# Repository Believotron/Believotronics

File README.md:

# Believotronics
[website](http://believotron.com/believotronics) | [donate](https://www.patreon.com/Believotron) | [community](http://community.believotron.com/c/believotronics)

Believotronics is a low-cost DIY open source robotics platform you can print and build at work or from home. Our first projects are a MicroscopeBot and a ThroughholeSolderBot.

We also develop mechatronics, jigs, firmware, assemblies, etc. Your basic toolkit for interfacing the physical world with the software world, allowing software to exist in physical space. Robots building robots. That sort of thing.

----
## Current Status

The current focus of the project is the [Core3D OpenSCAD Refactor](/Core3D/readme.md). We've designed the proof of concept using proprietary CAD tools, and now we'd like to convert them all to OpenSCAD, allowing for a much more flexible, modular, and ultimately scalable solution. Once we have the core system redesiged, we will start refactoring the [MircoscopeBot](/MircoscopeBot/.readme), and then then proceed with the [ThroughholeSolderBot](/ThroughholeSolderBot/readme.md)

Each project is maintained and documented in the project subdirectory.

Unless otherwise noted, this project uses the [MIT License](license).

[website](http://believotron.com/believotronics) | [donate](https://www.patreon.com/Believotron) | [community](http://community.believotron.com/c/believotronics)

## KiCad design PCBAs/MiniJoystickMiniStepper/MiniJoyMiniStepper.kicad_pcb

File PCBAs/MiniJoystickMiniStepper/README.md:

# Believotronics MiniJoystickMiniStepper
[website](http://believotron.com/believotronics) | [donate](https://www.patreon.com/Believotron) | [community](http://community.believotron.com/c/believotronics)

Believotronics is a low-cost DIY open source robotics platform you can print and build at work or from home. The MiniJoystickMiniStepper motor is a proof of concept to allow us to start prototyping controls using joysticks and driving motors with the ULM2803s.

Please [consider helping us with your financial support:](https://www.patreon.com/Believotron)

----
## Current Status

Phase 3 (Current): Pause
This project is on hold until the [Core3D](/Core3D/readme.md) refactoring project is complete.

Phase 4:
- Replace joysticks with gamepad style analog thumbsticks
- Increase channel count
- Insert serial buffer ICs to make code more platform agnostic
- Shrink board for Cortex M0 application
- Prototype LiPo / Lion 18650 (Protected) battery power
- Prototype initial Cortex M0 bootstrap (bypass using external controller

Phase 5:
- Add wireless support

[website](http://believotron.com/believotronics) | [donate](https://www.patreon.com/Believotron) | [community](http://community.believotron.com/c/believotronics)

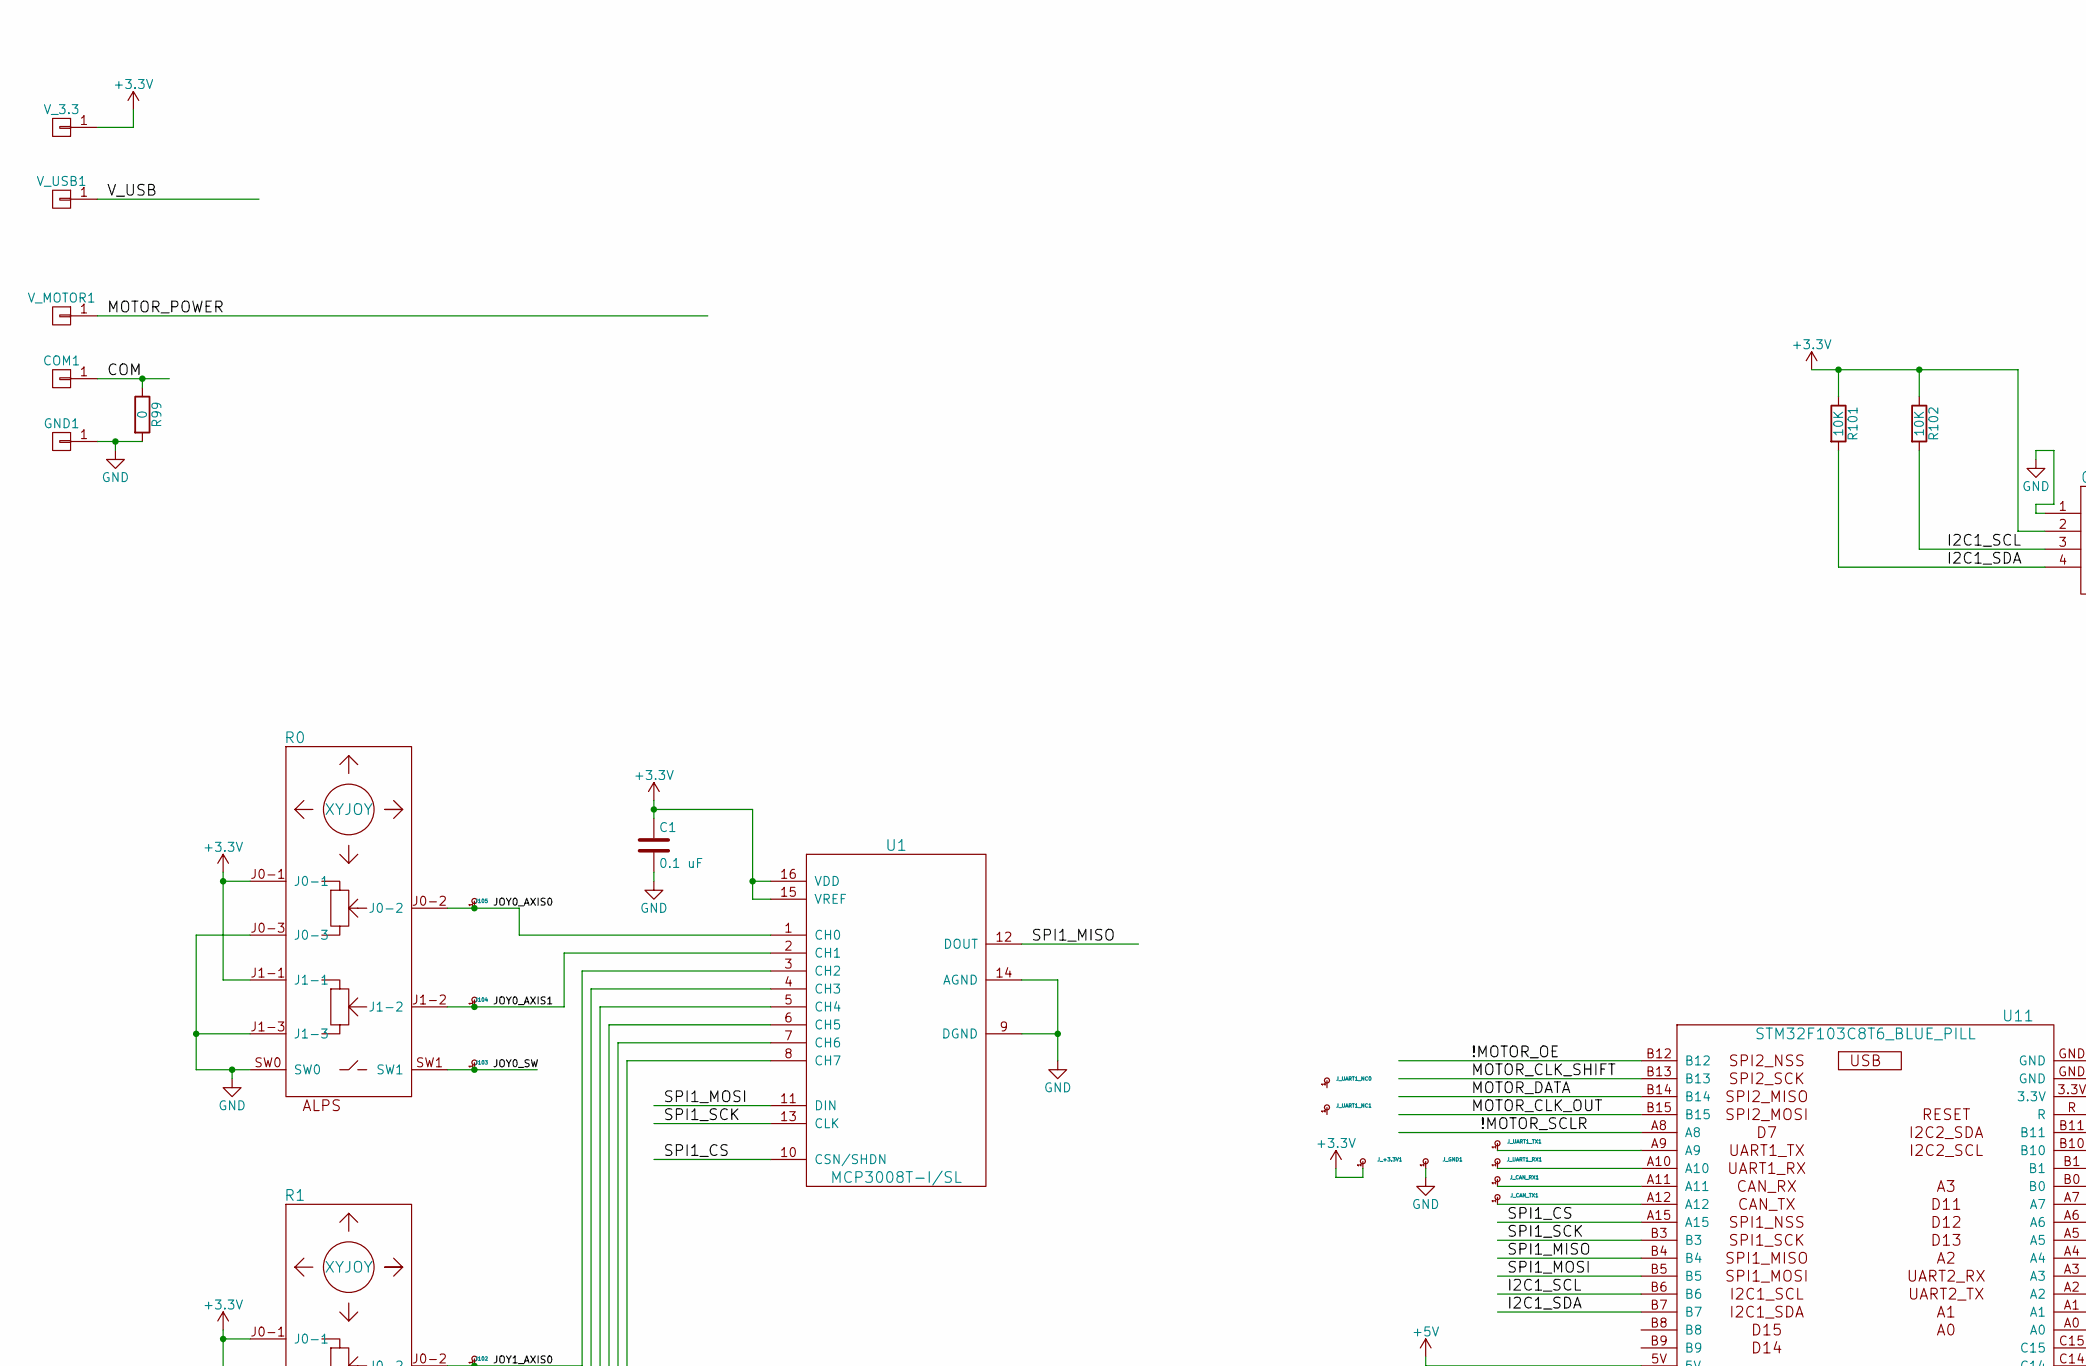
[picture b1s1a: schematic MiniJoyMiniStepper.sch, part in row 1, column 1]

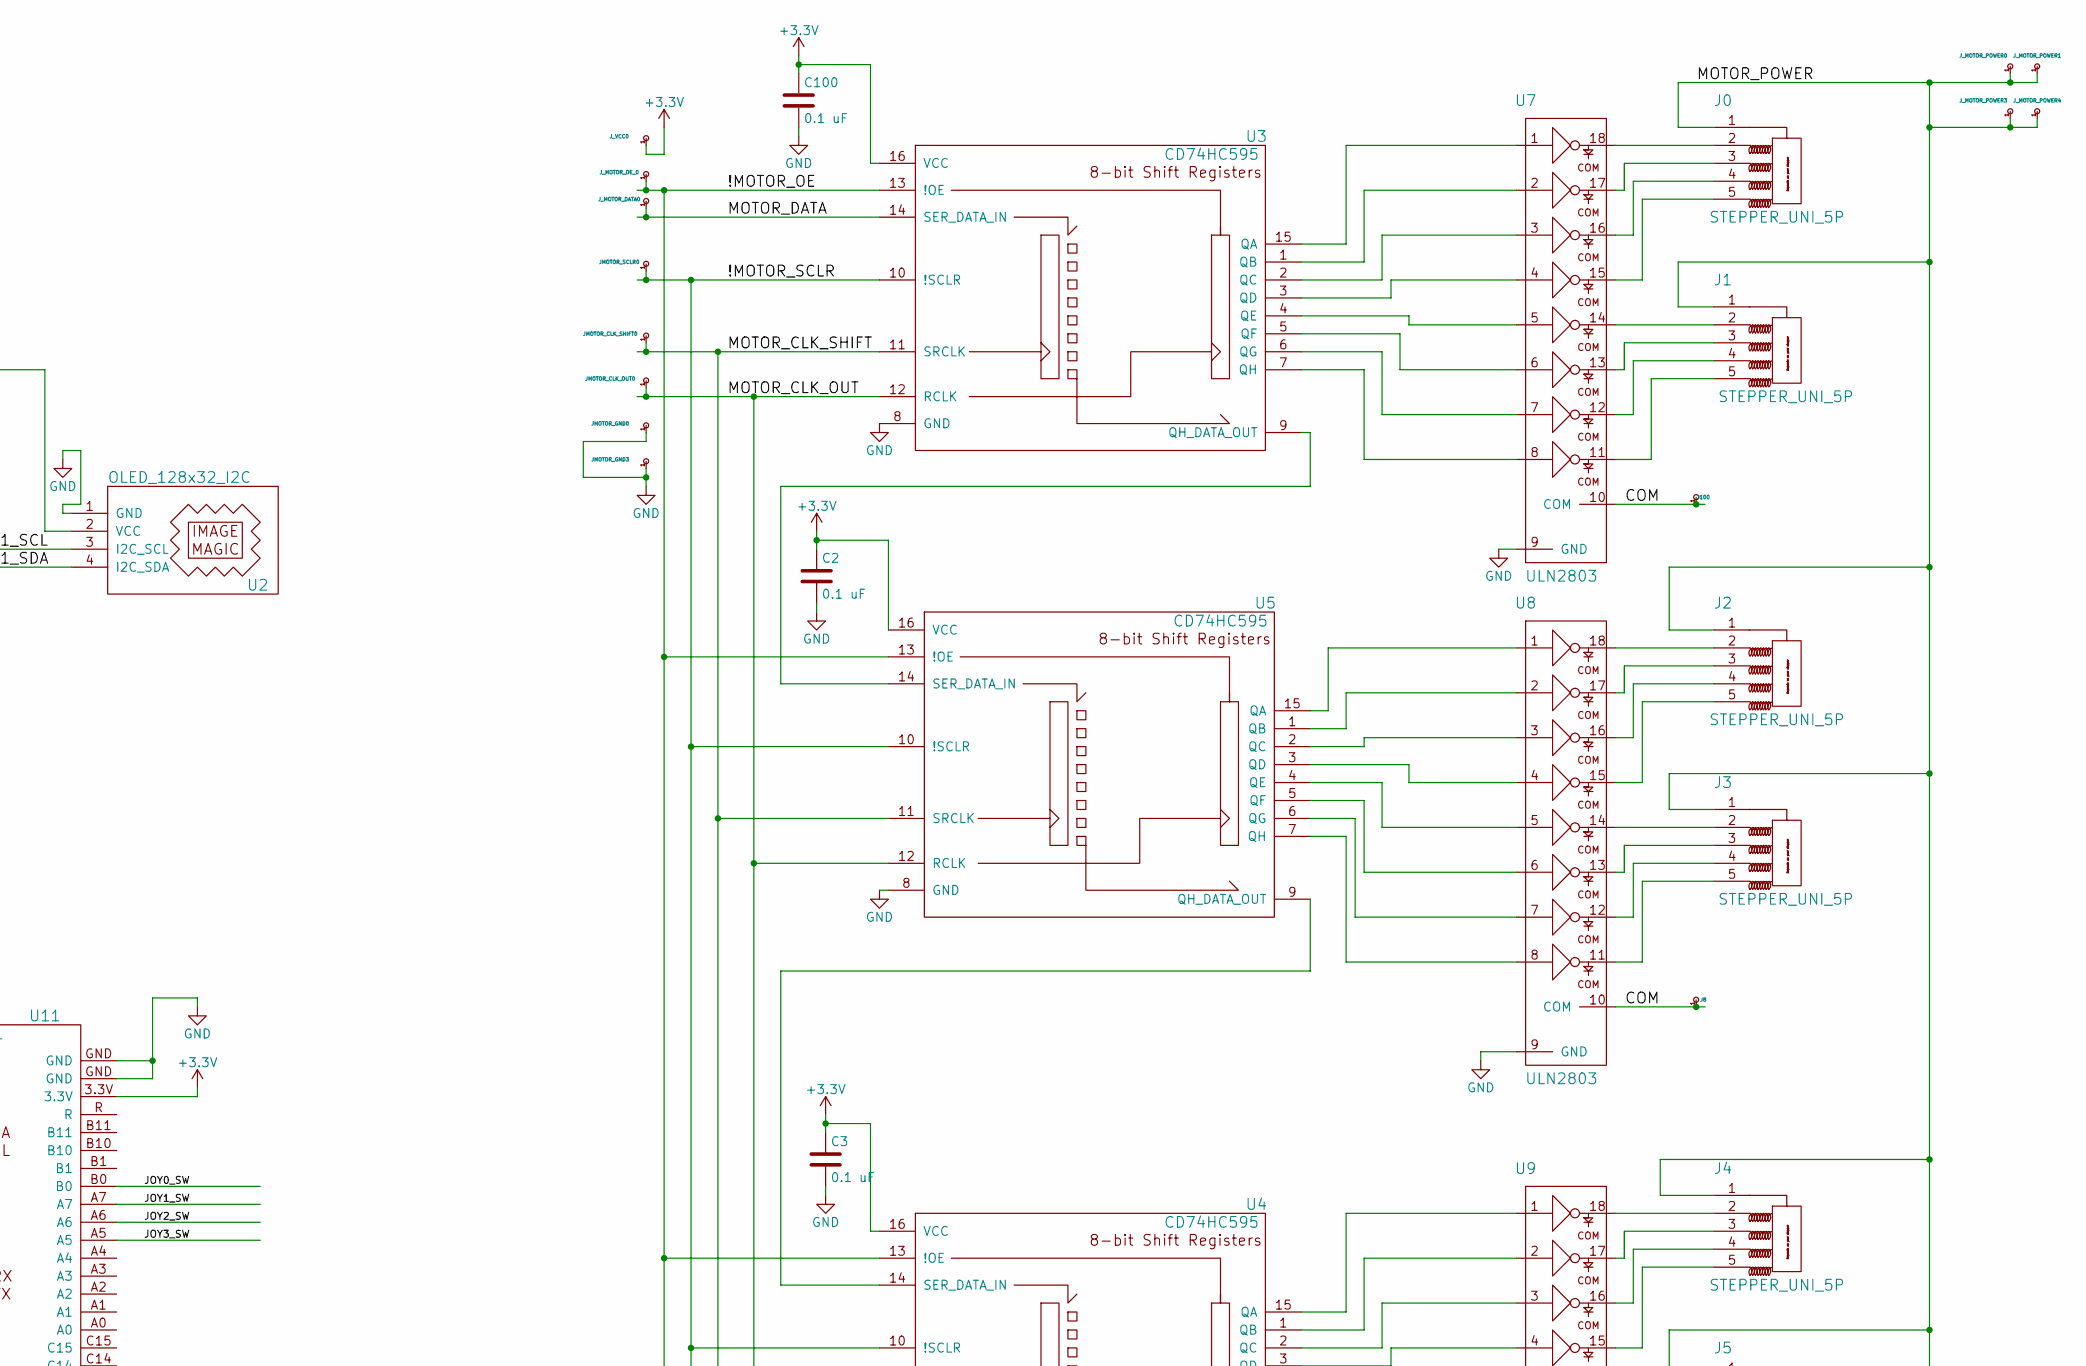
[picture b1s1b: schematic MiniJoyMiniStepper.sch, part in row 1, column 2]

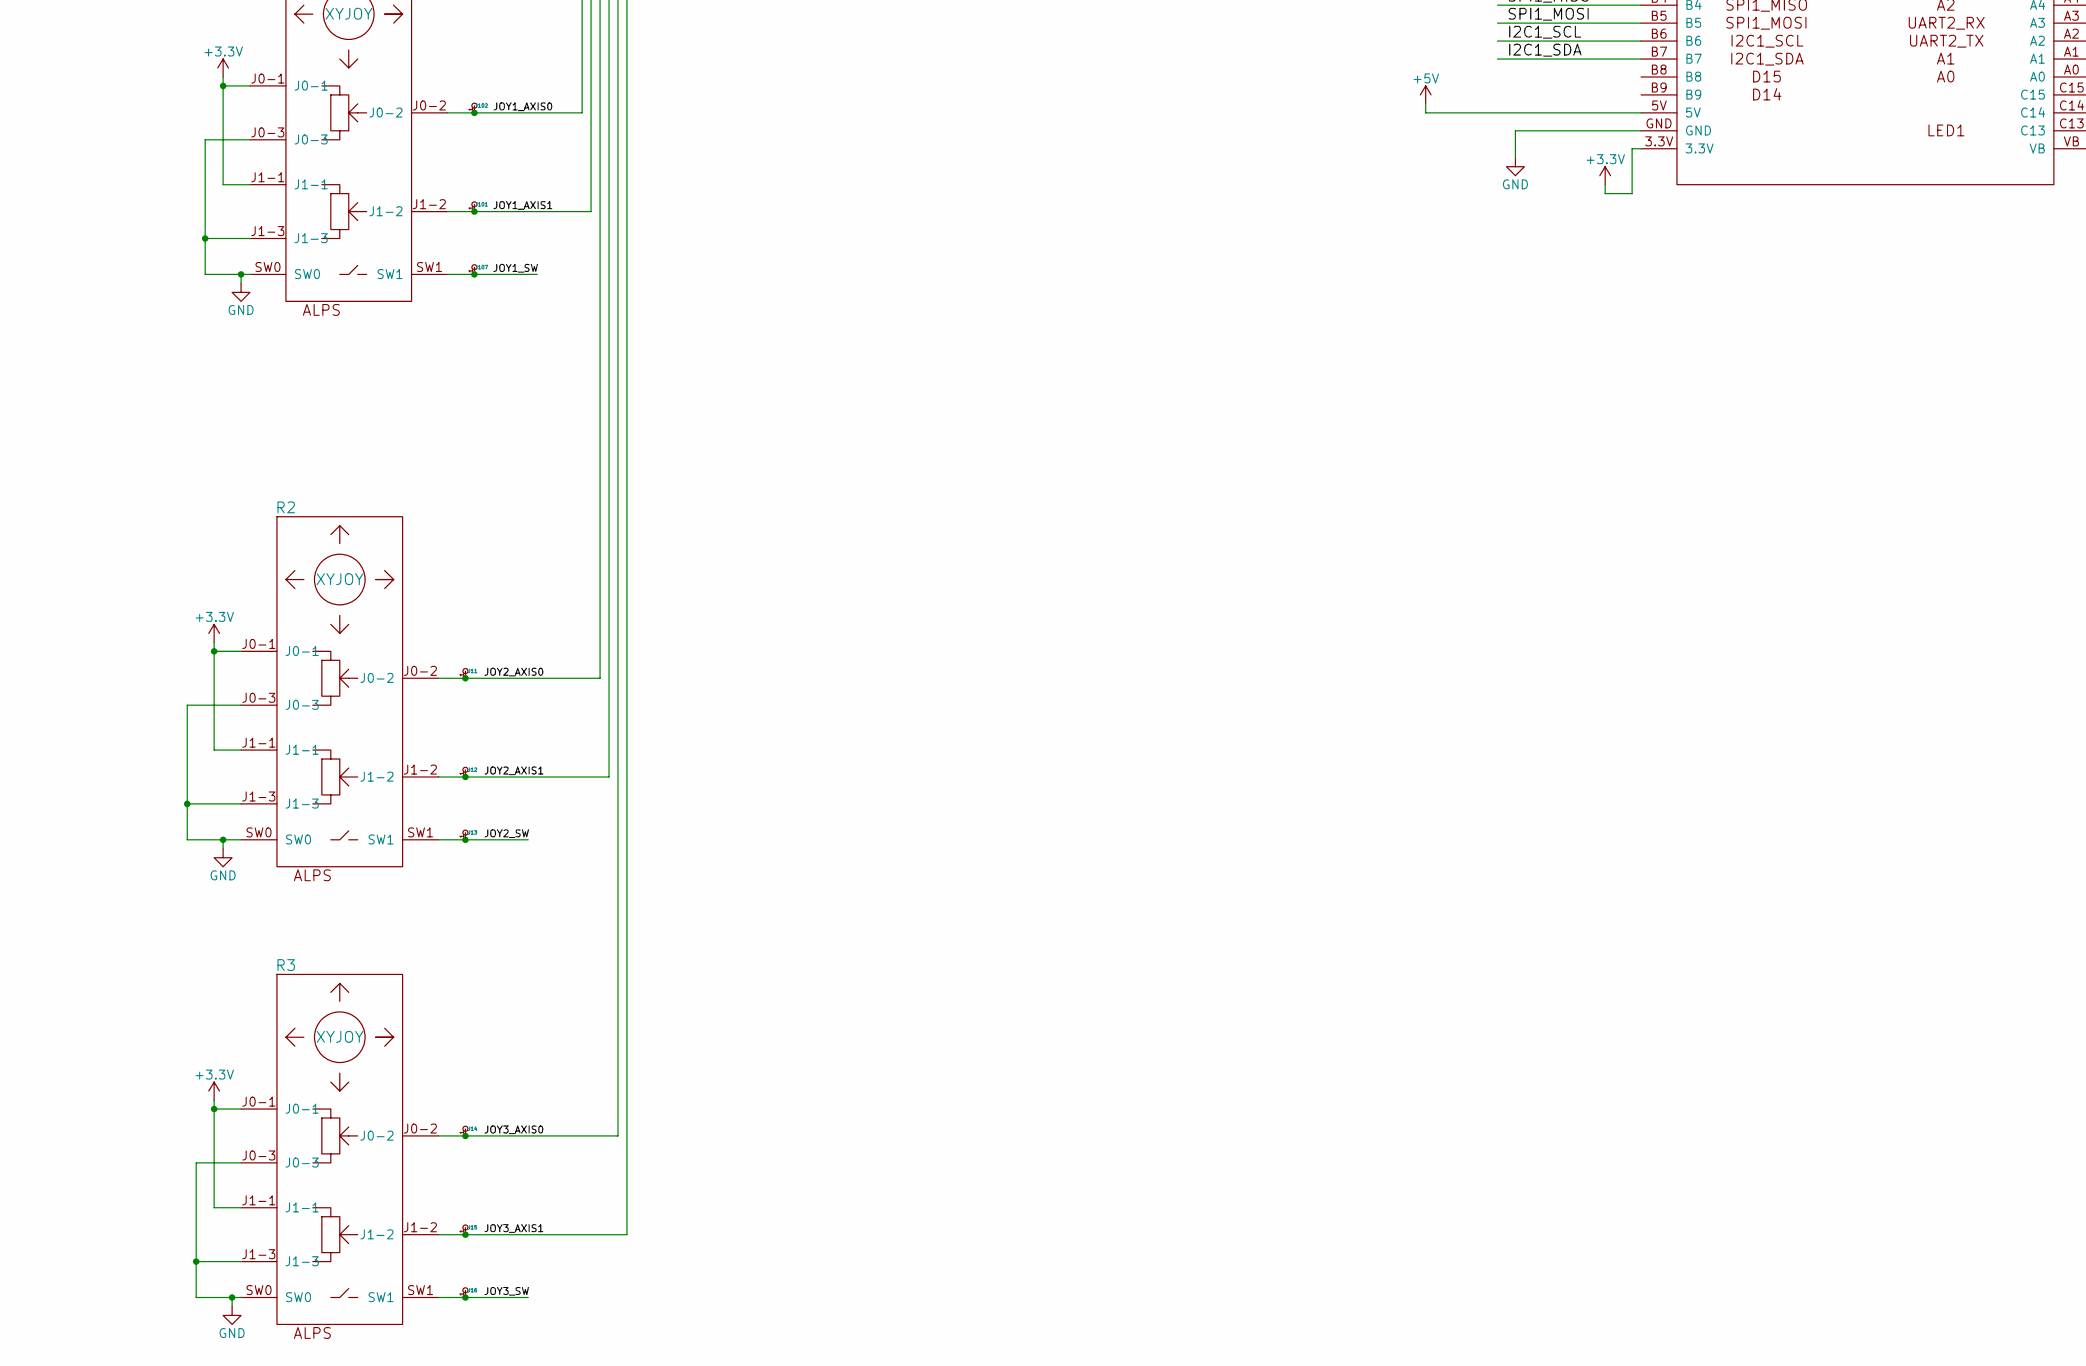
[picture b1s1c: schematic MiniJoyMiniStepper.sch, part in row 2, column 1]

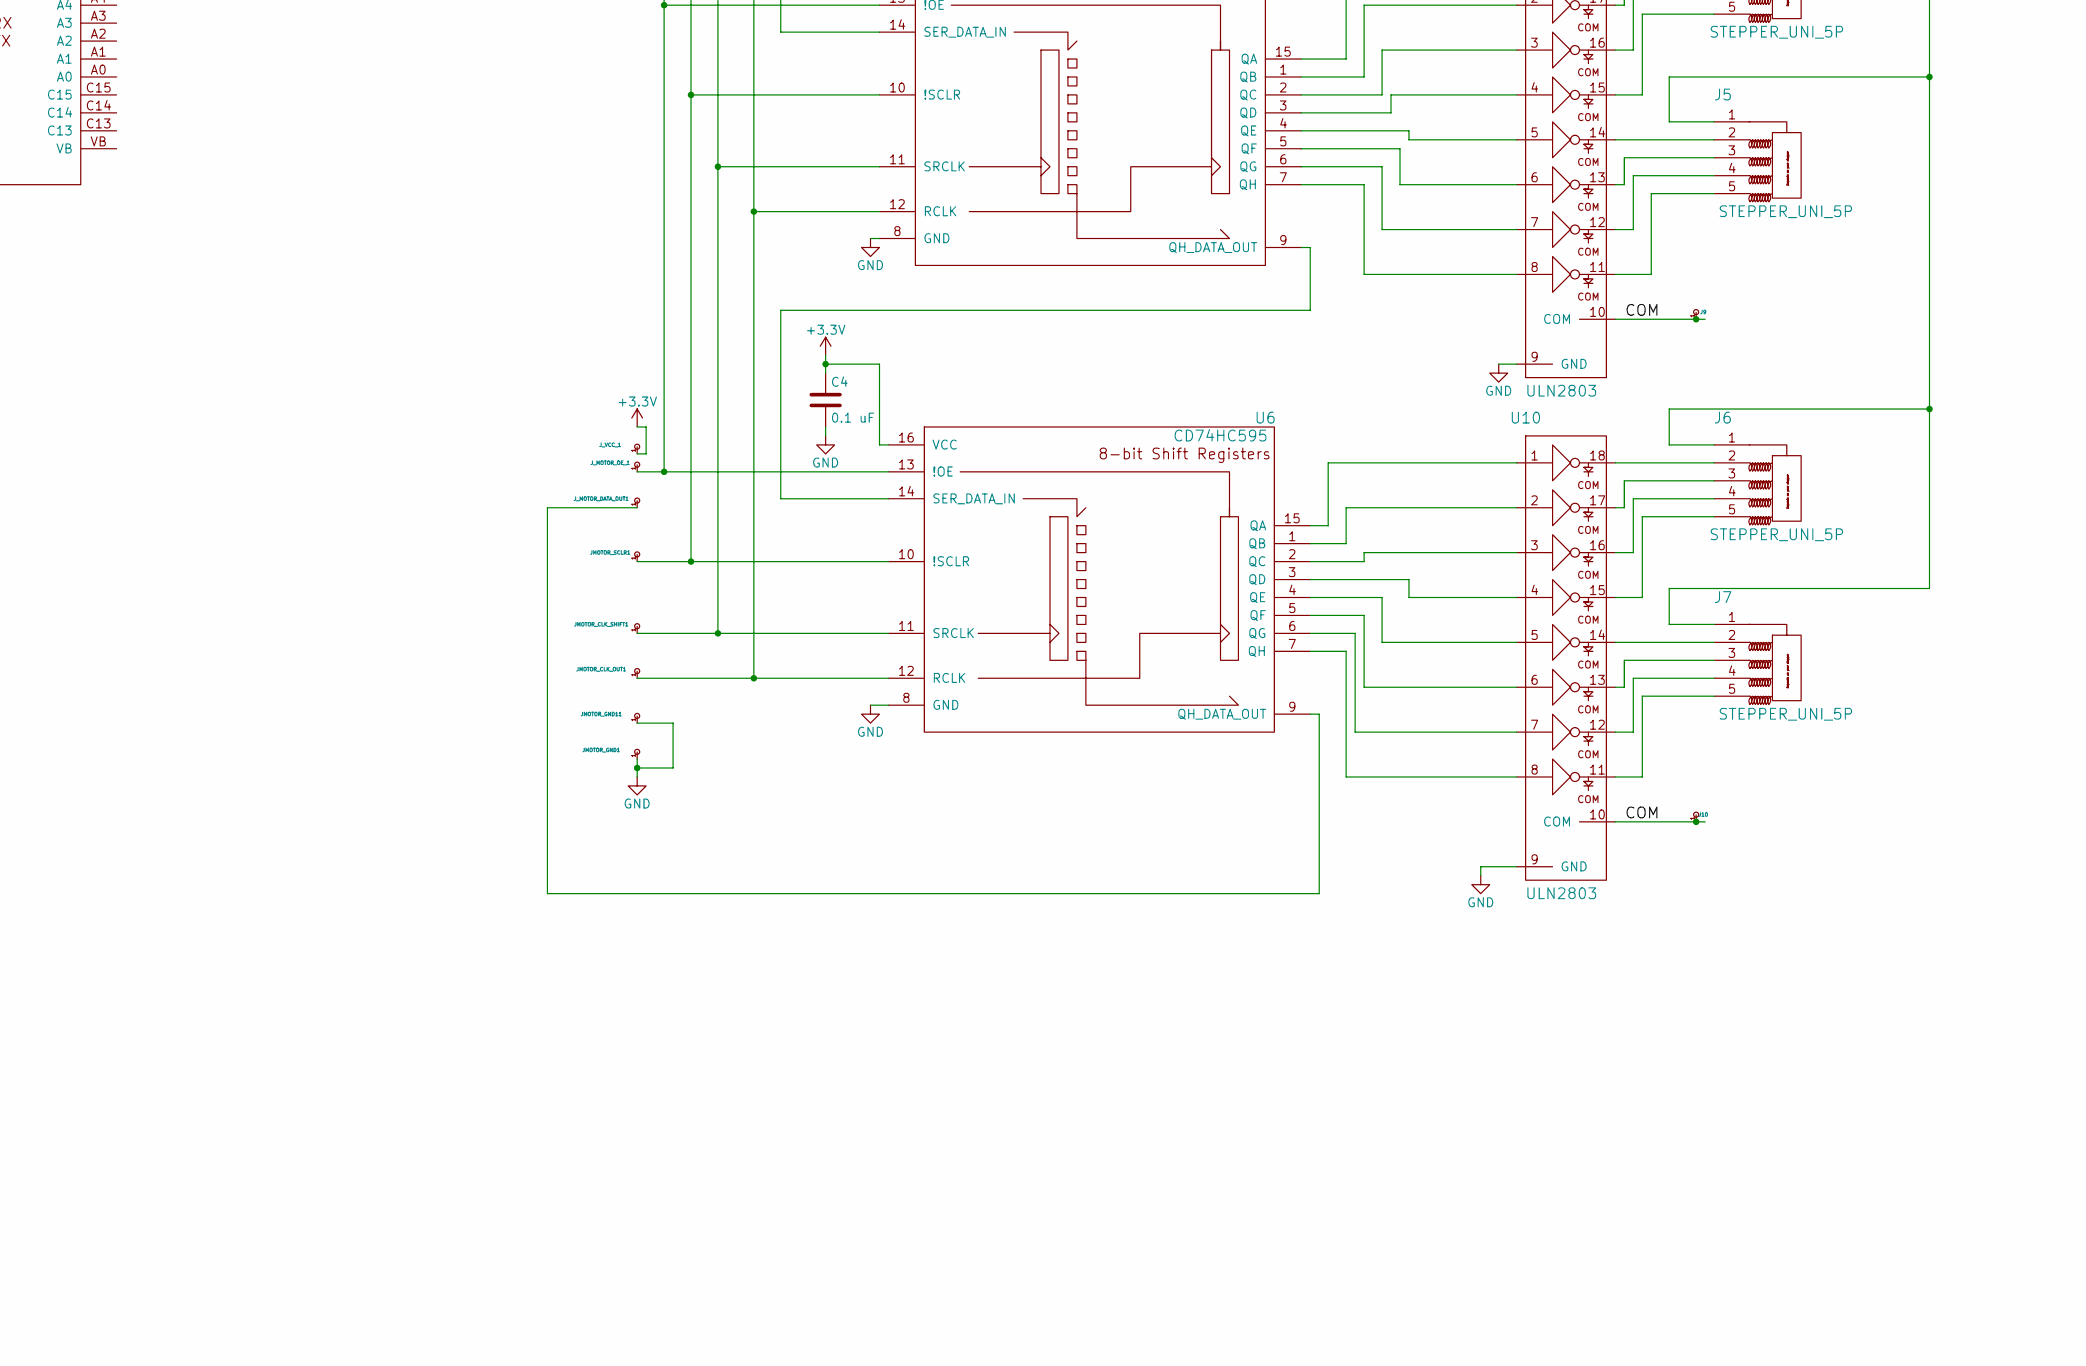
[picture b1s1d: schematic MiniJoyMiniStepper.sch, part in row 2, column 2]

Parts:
C1, C2, C3, C4, C100: 0.1 uF; C_0603; MPN CC0603KRX7R9BB104
COM1: CONN_01X01; TH_0.1_1x2_Jumper
GND1: CONN_01X01; TH_0.1_1x2_Jumper
J0, J1, J2, J3, J4, J5, J6, J7: STEPPER_UNI_5P; M20-1060500_DEBUG
J8, J9, J10, J11, J12, J13, J14, J15, J16, J100, J101, J102, J103, J104, J105, J107: TH_0.1_1x1; single_0.1
JMOTOR_CLK_OUT0, JMOTOR_CLK_OUT1: TH_0.1_1x1; single_0.1
JMOTOR_CLK_SHIFT0, JMOTOR_CLK_SHIFT1: TH_0.1_1x1; single_0.1
JMOTOR_GND0, JMOTOR_GND1, JMOTOR_GND3, JMOTOR_GND11: TH_0.1_1x1; single_0.1
JMOTOR_SCLR0, JMOTOR_SCLR1: TH_0.1_1x1; single_0.1
J_+3.3V1: TH_0.1_1x1; single_0.1
J_CAN_RX1: TH_0.1_1x1; single_0.1
J_CAN_TX1: TH_0.1_1x1; single_0.1
J_GND1: TH_0.1_1x1; single_0.1
J_MOTOR_DATA0: TH_0.1_1x1; single_0.1
J_MOTOR_DATA_OUT1: TH_0.1_1x1; single_0.1
J_MOTOR_OE_0, J_MOTOR_OE_1: TH_0.1_1x1; single_0.1
J_MOTOR_POWER0, J_MOTOR_POWER1, J_MOTOR_POWER3, J_MOTOR_POWER4: TH_0.1_1x1; single_0.1
J_UART1_NC0, J_UART1_NC1, J_UART1_RX1, J_UART1_TX1: TH_0.1_1x1; single_0.1
J_VCC0: TH_0.1_1x1; single_0.1
J_VCC_1: TH_0.1_1x1; single_0.1
R0, R1, R2, R3: XYJOY; JOY_ALPS_RKJXV1224005
R99: 0; R_0603; MPN CRCW06030000ZSTA
R101, R102: 10K; R_0603; MPN CRCW060310K0JNEA
U1: MCP3008T-I/SL; SOIC-16
U2: OLED_128x32_I2C; OLED_128x32
U3, U4, U5, U6: CD74HC595; SOIC-16_1.27x9.3
U7, U8, U9, U10: ULN2803; SOIC-18_1.27_9.4
U11: STM32F103C8T6_BLUE_PILL; BLUEPILL_CORTEXM3_STM32F103C8T6
V_3.3: CONN_01X01; TH_0.1_1x2_Jumper
V_MOTOR1: CONN_01X01; TH_0.1_1x2_Jumper
V_USB1: CONN_01X01; TH_0.1_1x2_Jumper

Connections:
+3V3: C1.1, C2.1, C3.1, C4.1, C100.1, J_+3.3V1.1, J_VCC0.1, J_VCC_1.1, R0.J0-1, R0.J1-1, R1.J0-1, R1.J1-1, R2.J0-1, R2.J1-1, R3.J0-1, R3.J1-1, R101.1, R102.1, U1.15 (VREF), U1.16 (VDD), U2.2 (VCC), U3.16 (VCC), U4.16 (VCC), U5.16 (VCC), U6.16 (VCC), U11.3.3V, V_3.3.1
+5V: U11.5V
/!MOTOR_OE: J_MOTOR_OE_0.1, J_MOTOR_OE_1.1, U3.13 (!OE), U4.13 (!OE), U5.13 (!OE), U6.13 (!OE), U11.B12
/!MOTOR_SCLR: JMOTOR_SCLR0.1, JMOTOR_SCLR1.1, U3.10 (!SCLR), U4.10 (!SCLR), U5.10 (!SCLR), U6.10 (!SCLR), U11.A8
/COM: COM1.1, J8.1, J9.1, J10.1, J100.1, R99.1, U7.10 (COM), U8.10 (COM), U9.10 (COM), U10.10 (COM); also elsewhere on the board
/I2C1_SCL: R102.2, U2.3 (I2C_SCL), U11.B6
/I2C1_SDA: R101.2, U2.4 (I2C_SDA), U11.B7
/JOY0_AXIS0: J105.1, R0.J0-2, U1.1 (CH0)
/JOY0_AXIS1: J104.1, R0.J1-2, U1.2 (CH1)
/JOY0_SW: J103.1, R0.SW1, U11.B0
/JOY1_AXIS0: J102.1, R1.J0-2, U1.3 (CH2)
/JOY1_AXIS1: J101.1, R1.J1-2, U1.4 (CH3)
/JOY1_SW: J107.1, R1.SW1, U11.A7
/JOY2_AXIS0: J11.1, R2.J0-2, U1.5 (CH4)
/JOY2_AXIS1: J12.1, R2.J1-2, U1.6 (CH5)
/JOY2_SW: J13.1, R2.SW1, U11.A6
/JOY3_AXIS0: J14.1, R3.J0-2, U1.7 (CH6)
/JOY3_AXIS1: J15.1, R3.J1-2, U1.8 (CH7)
/JOY3_SW: J16.1, R3.SW1, U11.A5
/MOTOR_CLK_OUT: JMOTOR_CLK_OUT0.1, JMOTOR_CLK_OUT1.1, U3.12 (RCLK), U4.12 (RCLK), U5.12 (RCLK), U6.12 (RCLK), U11.B15
/MOTOR_CLK_SHIFT: JMOTOR_CLK_SHIFT0.1, JMOTOR_CLK_SHIFT1.1, U3.11 (SRCLK), U4.11 (SRCLK), U5.11 (SRCLK), U6.11 (SRCLK), U11.B13
/MOTOR_DATA: J_MOTOR_DATA0.1, U3.14 (SER_DATA_IN), U11.B14
/MOTOR_POWER: J0.1, J1.1, J2.1, J3.1, J4.1, J5.1, J6.1, J7.1, J_MOTOR_POWER0.1, J_MOTOR_POWER1.1, J_MOTOR_POWER3.1, J_MOTOR_POWER4.1, V_MOTOR1.1
/SPI1_CS: U1.10 (CSN/SHDN), U11.A15
/SPI1_MISO: U1.12 (DOUT), U11.B4
/SPI1_MOSI: U1.11 (DIN), U11.B5
/SPI1_SCK: U1.13 (CLK), U11.B3
/V_USB: V_USB1.1
GND: C1.2, C2.2, C3.2, C4.2, C100.2, GND1.1, JMOTOR_GND0.1, JMOTOR_GND1.1, JMOTOR_GND3.1, JMOTOR_GND11.1, J_GND1.1, R0.J0-3, R0.J1-3, R0.SW0, R1.J0-3, R1.J1-3, R1.SW0, R2.J0-3, R2.J1-3, R2.SW0, R3.J0-3, R3.J1-3, R3.SW0, R99.2, U1.9 (DGND), U1.14 (AGND), U2.1 (GND), U3.8 (GND), U4.8 (GND), U5.8 (GND), U6.8 (GND), U7.9 (GND), U8.9 (GND), U9.9 (GND), U10.9 (GND), U11.GND
unnamed: J0.2, U7.18
unnamed: J0.3, U7.17
unnamed: J0.4, U7.16
unnamed: J0.5, U7.15
unnamed: J1.2, U7.14
unnamed: J1.3, U7.13
unnamed: J1.4, U7.12
unnamed: J1.5, U7.11
unnamed: J2.2, U8.18
unnamed: J2.3, U8.17
unnamed: J2.4, U8.16
unnamed: J2.5, U8.15
unnamed: J3.2, U8.14
unnamed: J3.3, U8.13
unnamed: J3.4, U8.12
unnamed: J3.5, U8.11
unnamed: J4.2, U9.18
unnamed: J4.3, U9.17
unnamed: J4.4, U9.16
unnamed: J4.5, U9.15
unnamed: J5.2, U9.14
unnamed: J5.3, U9.13
unnamed: J5.4, U9.12
unnamed: J5.5, U9.11
unnamed: J6.2, U10.18
unnamed: J6.3, U10.17
unnamed: J6.4, U10.16
unnamed: J6.5, U10.15
unnamed: J7.2, U10.14
unnamed: J7.3, U10.13
unnamed: J7.4, U10.12
unnamed: J7.5, U10.11
unnamed: J_CAN_RX1.1, U11.A11
unnamed: J_MOTOR_DATA_OUT1.1, U6.9 (QH_DATA_OUT)
unnamed: J_UART1_RX1.1, U11.A10
unnamed: J_UART1_TX1.1, U11.A9
unnamed: U3.1 (QB), U7.2
unnamed: U3.2 (QC), U7.3
unnamed: U3.3 (QD), U7.4
unnamed: U3.4 (QE), U7.5
unnamed: U3.5 (QF), U7.6
unnamed: U3.6 (QG), U7.7
unnamed: U3.7 (QH), U7.8
unnamed: U3.9 (QH_DATA_OUT), U5.14 (SER_DATA_IN)
unnamed: U3.15 (QA), U7.1
unnamed: U4.1 (QB), U9.2
unnamed: U4.2 (QC), U9.3
unnamed: U4.3 (QD), U9.4
unnamed: U4.4 (QE), U9.5
unnamed: U4.5 (QF), U9.6
unnamed: U4.6 (QG), U9.7
unnamed: U4.7 (QH), U9.8
unnamed: U4.9 (QH_DATA_OUT), U6.14 (SER_DATA_IN)
unnamed: U4.14 (SER_DATA_IN), U5.9 (QH_DATA_OUT)
unnamed: U4.15 (QA), U9.1
unnamed: U5.1 (QB), U8.2
unnamed: U5.2 (QC), U8.3
unnamed: U5.3 (QD), U8.4
unnamed: U5.4 (QE), U8.5
unnamed: U5.5 (QF), U8.6
unnamed: U5.6 (QG), U8.7
unnamed: U5.7 (QH), U8.8
unnamed: U5.15 (QA), U8.1
unnamed: U6.15 (QA), U10.1
unnamed: U6.1 (QB), U10.2
unnamed: U6.2 (QC), U10.3
unnamed: U6.3 (QD), U10.4
unnamed: U6.4 (QE), U10.5
unnamed: U6.5 (QF), U10.6
unnamed: U6.6 (QG), U10.7
unnamed: U6.7 (QH), U10.8

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
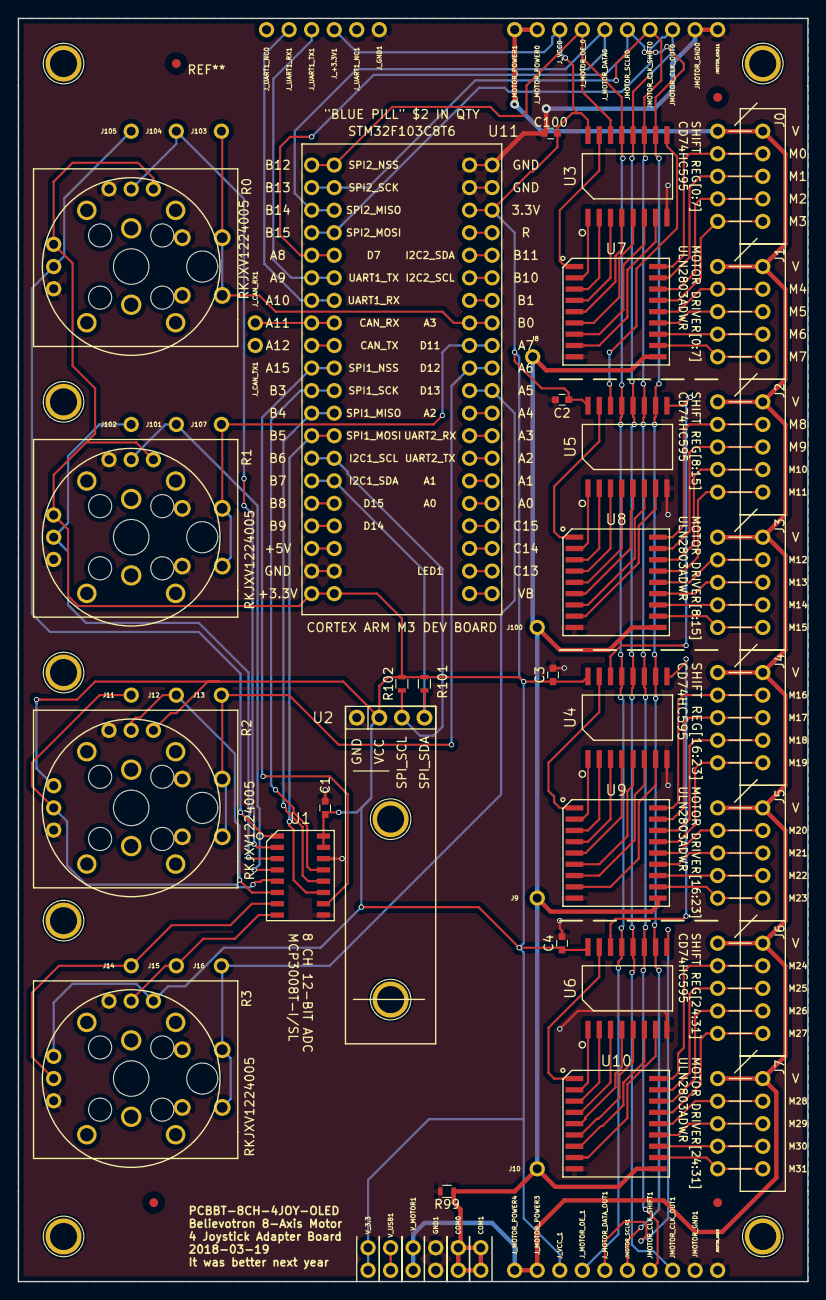
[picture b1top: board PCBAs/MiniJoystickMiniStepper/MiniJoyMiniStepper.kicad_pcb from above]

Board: 2 copper layers, 88.9 x 142.2 mm, 81 parts (0 on the bottom side), 98 nets.

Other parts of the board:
COM0: CONN_01X01; TH_0.1_1x2_Jumper

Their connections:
/COM: COM0.1; also elsewhere on the board

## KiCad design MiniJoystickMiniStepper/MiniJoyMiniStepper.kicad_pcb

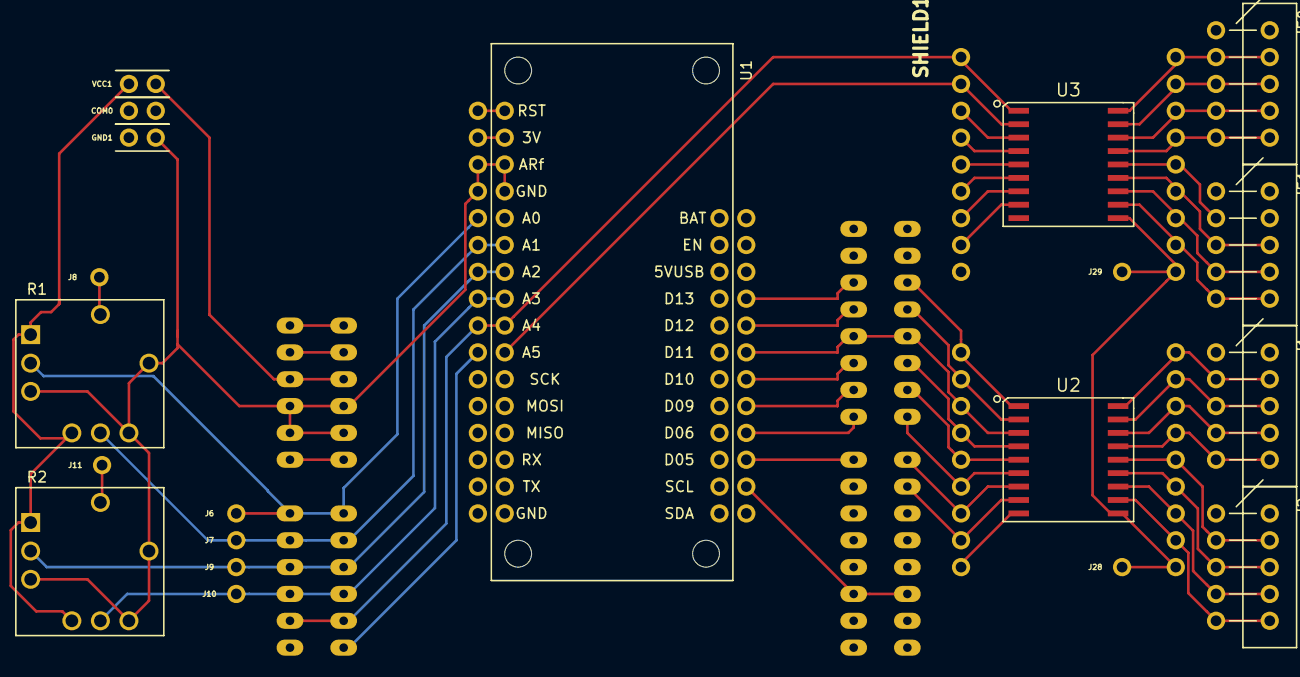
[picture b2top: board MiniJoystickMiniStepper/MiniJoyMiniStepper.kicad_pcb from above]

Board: 2 copper layers, 21 parts (0 on the bottom side), 41 nets.

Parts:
COM0: CONN_01X01; TH_0.1_1x2_Jumper
GND1: CONN_01X01; TH_0.1_1x2_Jumper
J1, J2, J50, J51: STEPPER_UNI_5P; M20-1060500_DEBUG
J6, J7, J8, J9, J10, J11, J28, J29: TH_0.1_1x1; single_0.1
R1, R2: XYJOY; XY_JOY_254TA103B50B
SHIELD1: ARDUINO_SHIELD; ARDUINO_SHIELD_2_debug
U1: ADAFRUIT_FEATHER_M0; ADAFRUIT_FEATHER_debug_1
U2, U3: ULN2803; SOIC-18_DEBUG
VCC1: CONN_01X01; TH_0.1_1x2_Jumper

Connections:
/COM: COM0.1, J28.1, J29.1, U2.10, U3.10
/JOY0_AXIS0: J6.1, R1.R1.2, SHIELD1.AD0, U1.A0
/JOY0_AXIS1: J7.1, R1.R2.2, SHIELD1.AD1, U1.A1
/JOY0_SW: J8.1, R1.S1.2
/JOY1_AXIS0: J9.1, R2.R1.2, SHIELD1.AD2, U1.A2
/JOY1_AXIS1: J10.1, R2.R2.2, SHIELD1.AD3, U1.A3
/JOY1_SW: J11.1, R2.S1.2
/M0_C0: SHIELD1.13, U1.D13, U2.1
/M0_C1: SHIELD1.12, U1.D12, U2.2
/M0_C2: SHIELD1.11, U1.D11, U2.3
/M0_C3: SHIELD1.10, U1.D10, U2.4
/M1_C0: SHIELD1.9, U1.D09, U2.5
/M1_C1: SHIELD1.8, U1.D06, U2.6
/M1_C2: SHIELD1.7, U1.D05, U2.7
/M1_C3: SHIELD1.6, U1.MISO, U2.8
/M2_C0: SHIELD1.AD5, U1.A4, U3.1
/M2_C1: SHIELD1.AD4, U1.A5, U3.2
/M2_C2: SHIELD1.5, U1.MOSI, U3.3
/M2_C3: SHIELD1.4, U1.SDA, U3.4
/M3_C0: SHIELD1.3, U1.SCK, U3.5
/M3_C1: SHIELD1.2, U1.SCL, U3.6
/M3_C2: SHIELD1.1, U1.TX, U3.7
/M3_C3: SHIELD1.0, U1.RX, U3.8
GND: GND1.1, R1.R1.3, R1.R2.3, R1.S1.1, R2.R1.3, R2.R2.3, R2.S1.1, SHIELD1.AREF, SHIELD1.GND1, SHIELD1.GND2, SHIELD1.GND3, U1.ARf, U1.GND, U2.9, U3.9
unnamed: J1.2, U2.18
unnamed: J1.3, U2.17
unnamed: J1.4, U2.16
unnamed: J1.5, U2.15
unnamed: J2.2, U2.14
unnamed: J2.3, U2.13
unnamed: J2.4, U2.12
unnamed: J2.5, U2.11
unnamed: J50.2, U3.18
unnamed: J50.3, U3.17
unnamed: J50.4, U3.16
unnamed: J50.5, U3.15
unnamed: J51.2, U3.14
unnamed: J51.3, U3.13
unnamed: J51.4, U3.12
unnamed: J51.5, U3.11
VCC: J1.1, J2.1, J50.1, J51.1, R1.R1.1, R1.R2.1, R2.R1.1, R2.R2.1, SHIELD1.5V, U1.USB, VCC1.1

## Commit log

2016-11-05 Basic one stepper motor, one-speed joystick Y motion
2016-12-31 Added SolderpasteRobot, MiniJoystickMiniStepper, and some code.
2017-01-01 Initial Placement. Some routing.
2017-01-01 More routing. 68 nets left.
2017-01-01 Finalized board. Ready for proto fab.
2017-02-11 Robot dev WIP.
2018-01-10 Added WIP TH Solder Robot 3D Files
2018-01-10 Channel 1 rotating in 1 direction, slowly.
2018-01-11 Added basic joystick support for 1 motor channel
2018-01-12 Bug keeping motor from moving. WIP 4 motor, 2 Joy infrastructure.
2018-01-12 4 Motor Channels working
2018-01-18 Swaped joystick axis controls
2018-02-06 Checking markdown rendering and linking on github website.
2018-02-06 Changed youtube embed b/c github doen't support embedding.
2018-02-06 Updated link format
2018-02-06 Updated video "embed"
2018-02-06 Reordered video link
2018-02-06 Added linebreak for readability.
2018-02-06 Removed double ":" in link
2018-02-06 Added images and basic project info to Microscopebot page
2018-02-06 Removed double video link
2018-02-06 updated image paths
2018-02-06 Fixed case sensetive file suffix issue.
2018-02-06 added formatting linebreak
2018-02-06 Updated badge text
2018-02-06 Added SolderpasteBot documentation / project update.
2018-02-06 Added "Core3D" to badge
2018-02-06 fixed image suffix case
2018-02-06 Corrected title to SolderpasteBot
2018-02-06 Added ThroughholeSolderBot readme documentation
2018-02-06 Organikzed files to CNC_Code folder
2018-02-06 Moved files to PCBAs folder to tidy up
2018-02-06 Moved MotorLab to CNC_Code folder
2018-02-06 Moved stale, unsorted file list to inbox directory
2018-02-06 Moved old solder paste files to \SolderpasteBot\lecagy to consolidate directories
2018-02-06 Moved XYRobotJoy to CNC_Code Directory
2018-02-06 Added MiniJoystickMiniStepper readme.md documentation
2018-02-06 Added missing image file
2018-02-06 Organized TH Solderbot 3D files
2018-02-06 Added core components to directory, awaiting conversion to OpenSCAD
2018-02-12 Added missing second story tab.
2018-02-12 Verified print works.
2018-02-16 Added shift register to library
2018-02-16 Added Prusa output
2018-02-20 Added ARM M0, Osc, Joystick, and other footprints/symbols
2018-02-21 Added STM32F103C8T6 Blue pill informative footprint
2018-02-21 Added STM32F103C8T6 Blue Pill schematic symbol
2018-02-22 Finished first pass schematic
2018-02-22 Added missing footprints to sch
2018-02-22 Fixed incorrect pin / net spelling
2018-02-22 90% PCB placement
2018-02-24 Added 0.1" header for daisy chaining shift register / motor driver.
2018-02-24 Replaced cut copy instead of copy paste accident. Added GND + VCC pins
2018-02-24 Added bypass caps to Shift Registers.
2018-02-24 Fixed cut/paste instead of copy/paste bug
2018-02-24 Placed Shift register daisy chain connectors
2018-02-24 Updated daisy chain con, added motor power and xtra gnd
2018-02-24 Updated daisy chain. Added extra motor power pins for more current/heat disspation.
2018-02-24 Added FTDI to USB interface. PCB ready for routing
2018-02-24 Updated PCB silkscreen. Added design sugar, part numbers, part function, better labeling
2018-02-24 Fixed PCB bug: Reconnected pads to nets
2018-03-05 Mid-route
2018-03-05 PCB mid-route
2018-03-06 PCB Midroute: Motor Driver + Shift Register routed.
2018-03-06 PCB Mid route
2018-03-07 PCB First route complete. Files not ready for fab.
2018-03-07 Sch: Fixed power net bug to joysticks. VCC->3.3V
2018-03-07 Added footprint. Bluepill thin profile
2018-03-19 Generated Gerbers. Ready for fab!
2018-03-20 Added forgotten soldermask layers
2018-05-21 Added original Prusa STL files for a baseline. This robot will be a mixture of original and modified files.
2018-05-21 Sticky save
2018-05-21 WIP Verifying prints on other printers
2018-05-21 Changed direction on various motors for demo
2018-05-21 WIP Developing generic X-Carriage for Prusa i3 MK2
2018-06-19 Added prusa 3d files
2018-06-19 Copied as a baseline for vibration control
2018-06-19 forked xinput.py for joystick control
2018-06-19 Hello world control of robot.
2018-06-19 Added troubleshooting
2018-06-19 Added basic X control
